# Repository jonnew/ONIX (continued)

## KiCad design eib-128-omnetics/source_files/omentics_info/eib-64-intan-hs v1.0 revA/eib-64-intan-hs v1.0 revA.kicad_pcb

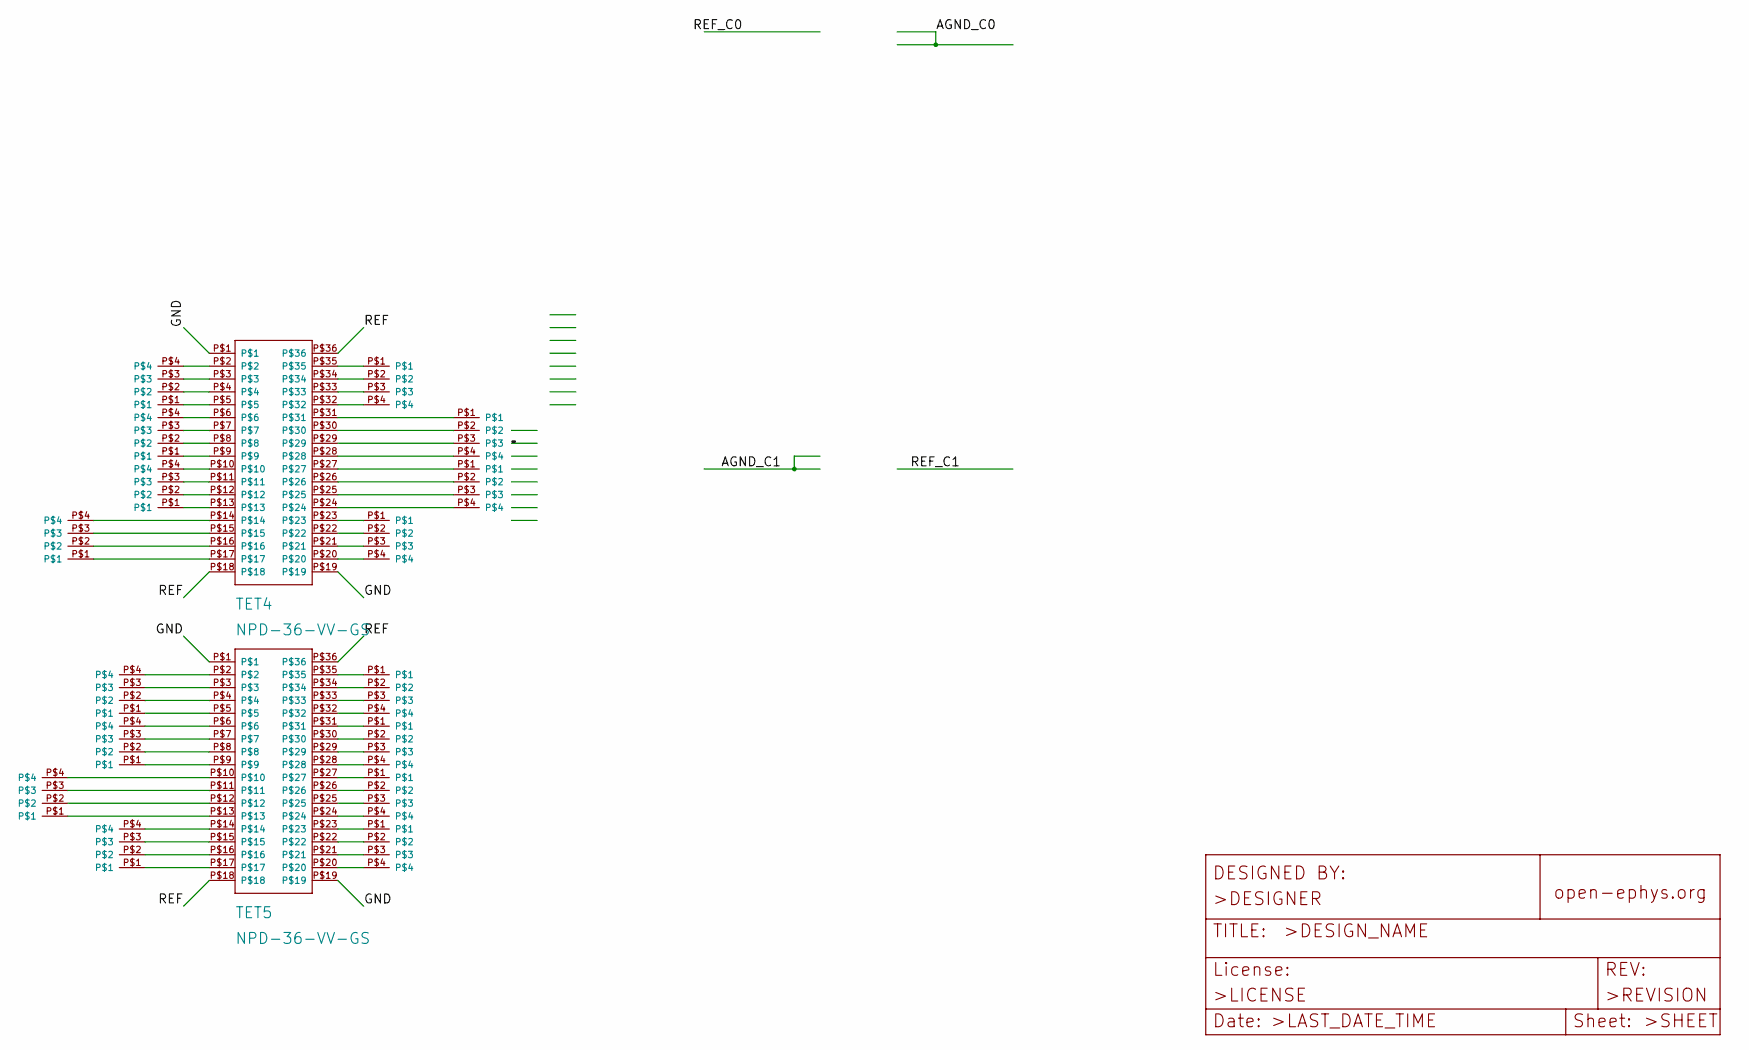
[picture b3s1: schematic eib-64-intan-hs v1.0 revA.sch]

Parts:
TET0: 0; TET32
TET1: 1; TET32
TET2: 2; TET32
TET3: 3; TET32
TET4, TET5: NPD-36-VV-GS
TET8: 8; TET32
TET9: 9; TET32
TET10: 10; TET32
TET11: 11; TET32
TET12: 12; TET32
TET13: 13; TET32
TET14: 14; TET32
TET15: 15; TET32
TET20: 20; TET32
TET21: 21; TET32
TET22: 22; TET32
TET23: 23; TET32

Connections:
/GND: TET4.P$1, TET4.P$19, TET5.P$1, TET5.P$19
/REF: TET4.P$18, TET4.P$36, TET5.P$18, TET5.P$36
unnamed: TET0.P$1, TET4.P$9
unnamed: TET0.P$2, TET4.P$8
unnamed: TET0.P$3, TET4.P$7
unnamed: TET0.P$4, TET4.P$6
unnamed: TET1.P$1, TET4.P$5
unnamed: TET1.P$2, TET4.P$4
unnamed: TET1.P$3, TET4.P$3
unnamed: TET1.P$4, TET4.P$2
unnamed: TET2.P$1, TET4.P$31
unnamed: TET2.P$2, TET4.P$30
unnamed: TET2.P$3, TET4.P$29
unnamed: TET2.P$4, TET4.P$28
unnamed: TET3.P$1, TET4.P$35
unnamed: TET3.P$2, TET4.P$34
unnamed: TET3.P$3, TET4.P$33
unnamed: TET3.P$4, TET4.P$32
unnamed: TET5.P$2, TET8.P$4
unnamed: TET5.P$3, TET8.P$3
unnamed: TET5.P$4, TET8.P$2
unnamed: TET5.P$5, TET8.P$1
unnamed: TET5.P$6, TET9.P$4
unnamed: TET5.P$7, TET9.P$3
unnamed: TET5.P$8, TET9.P$2
unnamed: TET5.P$9, TET9.P$1
unnamed: TET5.P$35, TET10.P$1
unnamed: TET5.P$34, TET10.P$2
unnamed: TET5.P$33, TET10.P$3
unnamed: TET5.P$32, TET10.P$4
unnamed: TET5.P$31, TET11.P$1
unnamed: TET5.P$30, TET11.P$2
unnamed: TET5.P$29, TET11.P$3
unnamed: TET5.P$28, TET11.P$4
unnamed: TET5.P$27, TET12.P$1
unnamed: TET5.P$26, TET12.P$2
unnamed: TET5.P$25, TET12.P$3
unnamed: TET5.P$24, TET12.P$4
unnamed: TET5.P$23, TET13.P$1
unnamed: TET5.P$22, TET13.P$2
unnamed: TET5.P$21, TET13.P$3
unnamed: TET5.P$20, TET13.P$4
unnamed: TET5.P$13, TET14.P$1
unnamed: TET5.P$12, TET14.P$2
unnamed: TET5.P$11, TET14.P$3
unnamed: TET5.P$10, TET14.P$4
unnamed: TET5.P$17, TET15.P$1
unnamed: TET5.P$16, TET15.P$2
unnamed: TET5.P$15, TET15.P$3
unnamed: TET5.P$14, TET15.P$4
unnamed: TET4.P$23, TET20.P$1
unnamed: TET4.P$22, TET20.P$2
unnamed: TET4.P$21, TET20.P$3
unnamed: TET4.P$20, TET20.P$4
unnamed: TET4.P$27, TET21.P$1
unnamed: TET4.P$26, TET21.P$2
unnamed: TET4.P$25, TET21.P$3
unnamed: TET4.P$24, TET21.P$4
unnamed: TET4.P$17, TET22.P$1
unnamed: TET4.P$16, TET22.P$2
unnamed: TET4.P$15, TET22.P$3
unnamed: TET4.P$14, TET22.P$4
unnamed: TET4.P$13, TET23.P$1
unnamed: TET4.P$12, TET23.P$2
unnamed: TET4.P$11, TET23.P$3
unnamed: TET4.P$10, TET23.P$4

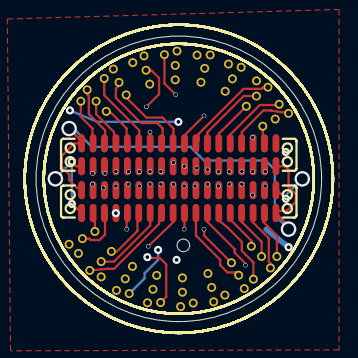
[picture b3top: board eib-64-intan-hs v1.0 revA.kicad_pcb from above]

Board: 4 copper layers, 15.9 x 15.9 mm, 19 parts (0 on the bottom side), 66 nets.

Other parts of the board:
@HOLE0: (no value)

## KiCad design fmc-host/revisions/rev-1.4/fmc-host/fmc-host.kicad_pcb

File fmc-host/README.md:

:warning: This headstage has moved to a dedicated repository: https://github.com/open-ephys/onix-fmc-host.
This folder should be considered archived.

# FMC Host Board
This card serves as host interface for serialized headstages and miniscopes, as
well as general purpose analog and digital IO. This board is a VITA-57.1
compliant module that uses high pin-count FMC connector. In combination with a
base FPGA board (e.g. [Numato Lab
Nereid](https://numato.com/product/nereid-kintex-7-pci-express-fpga-development-board),
it provides host PC communication for the following:

- Two deserailizers for any multifunction headstage conforming to our
  serialization protocol
- 12x 16-bit, +/-10V analog outputs or inputs. Direction selected via analog
  switch controllable over the FMC connector. Analog inputs are separated into
  2 simultaneously sampled 6-channel banks. When analog outputs are used, they
  are are always looped back using the analog inputs.
- 3x high speed LVDS input pairs
- 2x high speed LVDS outputs pairs
- 2x high speed, arbitrary logic-level, singled-ended lock inputs
- 1x high speed single ended, 50 ohm clock output
- 4x MLVDS input or output trigger lines

Easy access to IO is provided by the [breakout board](../breakout/README.md).

## Gerber Files
{% include gerber_layers.md %}

## Bill of Materials
The bill of materials for this device can be found
[here](https://docs.google.com/spreadsheets/d/1F-KWcdvH_63iXjZf0cgCfDiFX6XXW3qw6rlR8DZrFpQ/edit#gid=1976092058).

## Manufacturing Requirements
In order to meet approximately correct trace impedances, the design assumes the following stackup:

1. Top Copper 0.035 mm
1. Prepreg (2313\*1) 0.1 mm
1. Inner Copper 0.0175 mm
1. Core (Copper) 0.565 mm
1. Inner Copper 0.0175 mm
1. Prepeg (2116\*1) 0.127 mm
1. Inner Copper 0.0175 mm
1. Core (Copper) 0.565 mm
1. Inner Copper 0.0175 mm
1. Prepreg (2313\*1) 0.1 mm
1. Bottom Copper 0.0175 mm

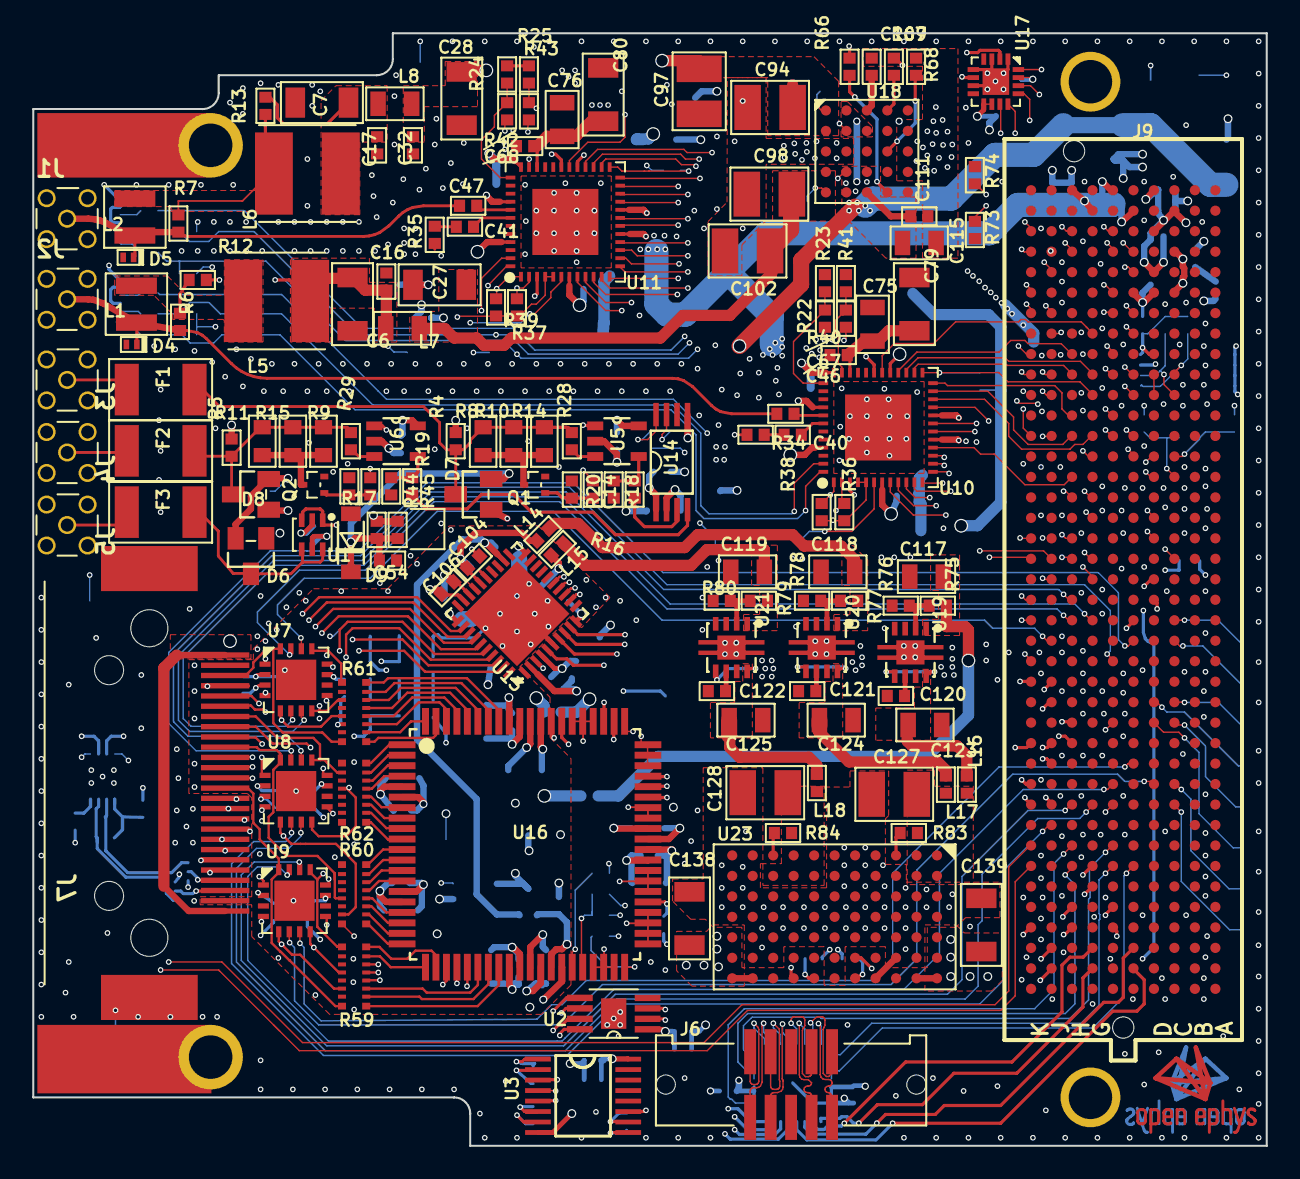
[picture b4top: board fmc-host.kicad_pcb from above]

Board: 6 copper layers, 76.5 x 69.0 mm, 321 parts (0 on the bottom side), 305 nets.

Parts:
C1, C2, C6, C7, C27, C28, C35, C36, C37, C38, C72, C73, C79, C80, C81, C91, C92, C138, C139, C140, C141: 10uF; 1206
C3, C4, C8, C9, C10, C11, C14, C15, C16, C17, C18, C19, C20, C23, C24, C31, C32, C33, C34, C39, C43, C45, C46, C47, C48, C49, C50, C51, C54, C55, C56, C58, C60, C62, C63, C65, C66, C67, C68, C78, C83, C84, C85, C86, C87, C89, C90, C93, C99, C100, C104, C106, C109, C110, C111, C113, C114, C129, C130, C131, C133, C134, C136, C137: 0.1uF; 0402
C5, C29, C30: 4.7nF; 0402
C12, C13, C21, C22, C25, C26, C52, C53, C57, C59, C82, C120, C121, C122: 10nF; 0402
C40, C41: 47nF; 0402
C42, C44, C69, C70, C74, C75, C76, C88: 1uF; 0805
C61, C64, C71, C77, C95, C96, C101, C103, C105, C107, C108, C112, C115, C116, C117, C118, C119, C123, C124, C125: 10uF; 0805
C94, C97, C98, C102, C126, C127, C128, C132, C135: 47uF; 1210
D1, D2, D3: HSMG-C280; LED-0402
D4, D5: SESD0402X1UN-0020-090; 0402P-DFN
D6, D7, D8: BAR66; SOT23
D9: KDZ4.3B; SOD123
D10, D11: APFA3011-AK13/F; RGB_LED_SMD-6
F1, F2, F3: C014F-2; 1812
J1, J2, J3, J4, J5: SMA002; MMCX-THRU
J6: ESHF-105-01-L-D-SM-K-TR
J7: 12226-8250-00FR; 12226-82X0-00XX
J8: 95278-101A16LF; JP2X8_SMD
J9: ASP-134488-01; FMC_HPC_MALE
L1, L2: 1008PS-472; 1008PS
L3, L4, L9, L10, L11, L12: BLM18KG601SN1D; 0603
L5, L6: SRNxx-101M; SRN6045TA
L7, L8: MPZ2012S102AT000; 0805
L13, L14, L15, L16, L17, L18: BLM15PX601SN1D; 0402
Q1, Q2: SI1012R; SC75
R1, R6, R7, R12, R13, R63, R64, R81, R82: 2k; 0402
R2, R3, R36, R37, R38, R39, R46, R49, R76, R78, R80: 4.7k; 0402
R4, R5, R23, R33, R44, R45: 3k; 0402
R8, R9, R10, R11, R14, R15: 150,0.25W; 0603
R16, R17, R55, R56, R57, R58, R83: 165k; 0402
R18, R19, R22, R40, R42, R65, R70, R71, R72, R73, R74, R85, R86: 10k; 0402
R20, R21, R47, R48, R50, R51, R52, R53: 1k; 0402
R24: 5.6k 1%; 0402
R25: 21k 1%; 0402
R26, R27: 60 1%; 0402
R28, R29, R34, R35: 49.9; 0402
R30, R31, R32: 100; 0402
R41, R43, R54, R69: 0; 0402
R59, R60, R61, R62: 2.2k; RN2X8-1506
R66, R67: 3.48k; 0402
R68: 649k; 0402
R75: 15k; 0402
R77, R79: 43k; 0402
R84: 178k; 0402
R87, R88: 73.2k; 0402
S1, S2: CHS-01TA; DIP01-SMD-GULL
S3: CHS-02TB
SJ1, SJ2: SJ2_0201; SJ_2_0201
TP1, TP2, TP4, TP5, TP6, TP7, TP11, TP12, TP13, TP14, TP15, TP16: TPB1,27; B1,27
TP3, TP8, TP9, TP10, TP17, TP18: TPB2,54; B2,54
U1: NC7WZ07P6X; SC70
U2: SN65LVDS9638DGN; MSOP-8-PAD-3X3
U3: FIN1032MTCX; TSSOP-16
U4: LTC2875_DFN; DFN83X3
U5, U6: ADCMP600; SOT-23-5
U7, U8, U9: DG1412E; QFN16-4X4MM
U10, U11: DS90UB934-Q1; WQFN48-7X7-PAD
U12: DS91M040; WQFN32-5X5
U13: AD5766BCPZ-RL7; CP_40_7
U14: MCP47FEB02A0-E/ST; TSSOP-8
U15: LM4132AMF-2.5/NOPBCT-ND; SOT-23-5
U16: AD7617BSTZ; ST_80_2
U17: AD5142BCPZ10; CP_16_27-L
U18: LTM4622A; BGA_5X5_625X625
U19, U20: TPS7A49; PVSON-N8+4-3X3
U21: TPS7A30; PVSON-N8+4-3X3
U22: 24ST; TSSOP8
U23: LTM8049_BGA; LTM8049
X2, X3: OE-LOGO_7X5; OE-LOGO-7X5
X4: FMC_SINGLE_WIDTH_MODULE

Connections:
+1V8: C86.2, C87.2, C91.2, C92.2, C135.2, C136.2, C137.2, J9.E39, J9.F40, J9.G39, J9.H40, L3.2, L4.2, L9.1, L10.1, R22.1, R24.1, R40.1, R42.1, TP16.TP, U10.17, U11.17
+3V3: C11.2, C23.1, C24.1, C29.1, C30.1, C33.1, C34.1, C39.1, C74.2, C78.2, C82.2, C89.2, C93.2, C96.2, C110.2, C112.2, C113.2, C116.2, C132.2, C133.2, C134.2, C138.1, C139.1, J9.C39, J9.D36, J9.D38, J9.D40, L11.1, L12.1, R36.2, R37.2, R38.2, R39.2, R46.2, R49.2, R63.2, R64.2, R69.1, R70.1, R71.1, R85.2, R86.2, S1.2, S2.2, TP11.TP, U1.5, U2.1, U3.4, U3.16, U4.3, U5.5, U6.5, U10.4, U10.5, U11.4, U11.5, U12.11, U12.12, U12.29, U12.30, U13.4, U14.1, U14.2, U16.49, U17.9, U17.10, U17.15, U23.A5, U23.A6, U23.A7, U23.B7, U23.K7, U23.L5, U23.L6, U23.L7
+12V: C115.2, C126.2, C129.2, C130.2, J7.1, J7.26, J9.C35, J9.C37, R44.2, R45.2, TP12.TP, U18.A2, U18.B3, U18.D3, U18.E2
/+5V_AN: C61.2, C64.2, C71.2, C77.2, C81.1, C83.2, C84.2, C85.2, C90.2, C106.2, C107.2, L13.1, R1.2, TP1.TP, U13.28, U15.3, U15.4, U16.6, U16.15, U16.30, U16.71
/+13V_AN: C8.2, C9.2, C10.2, C104.2, C105.2, L14.1, R2.2, TP2.TP, U7.11, U8.11, U9.11, U13.26
/-13V_AN: C18.2, C19.2, C20.2, C99.2, C103.2, L15.1, R3.2, TP4.TP, U7.2, U7.PAD, U8.2, U8.PAD, U9.2, U9.PAD, U13.6, U13.PAD
/ADC_BUSY: J9.J12, U16.67
/ADC_CONVST: J9.K13, U16.68
/ADC_MISO_A: J9.K11, U16.57
/ADC_MISO_B: J9.J10, U16.56
/ADC_MOSI: J9.K10, U16.55
/ADC_SCLK: J9.J13, U16.62
/ADDR0: J9.C27, R85.1, S3.4
/ADDR1: J9.C26, R86.1, S3.3
/AIN_AOUT0: J9.H19, U7.15
/AIN_AOUT1: J9.G19, U7.6
/AIN_AOUT2: J9.J18, U7.14
/AIN_AOUT3: J9.H20, U7.7
/AIN_AOUT4: J9.F17, U8.14
/AIN_AOUT5: J9.G10, U8.7
/AIN_AOUT6: J9.J9, U8.6
/AIN_AOUT7: J9.E18, U8.15
/AIN_AOUT8: J9.H10, U9.14
/AIN_AOUT9: J9.E12, U9.7
/AIN_AOUT10: J9.D11, U9.6
/AIN_AOUT11: J9.F11, U9.15
/AIO_0: J7.7, R59.C1, U9.16
/AIO_1: J7.20, R59.C3, U9.5
/AIO_2: J7.8, R59.C5, U9.8
/AIO_3: J7.21, R59.C8, U9.13
/AIO_4: J7.9, R60.C4, U8.16
/AIO_5: J7.22, R60.C2, U8.5
/AIO_6: J7.10, R62.C5, U8.8
/AIO_7: J7.23, R62.C7, U8.13
/AIO_8: J7.11, R61.C6, U7.8
/AIO_9: J7.24, R61.C8, U7.13
/AIO_10: J7.12, R61.C4, U7.5
/AIO_11: J7.25, R61.C1, U7.16
/AOUT0: U7.1, U13.32
/AOUT1: U7.4, U13.33
/AOUT2: U7.9, U13.34
/AOUT3: U7.12, U13.35
/AOUT4: U8.1, U13.36
/AOUT5: U8.4, U13.37
/AOUT6: U8.12, U13.38
/AOUT7: U8.9, U13.39
/AOUT8: U9.9, U13.12
/AOUT9: U9.12, U13.13
/AOUT10: U9.4, U13.14
/AOUT11: U9.1, U13.15
/CAN_RX: J9.K8, U4.4
/CAN_TX: J9.K7, U4.1
/CLKIN0: J9.D21, TP7.TP, U5.1
/CLKIN1: J9.E19, TP6.TP, U6.1
/CLKIN_TERM0: J9.K19, R20.1
/CLKIN_TERM1: J9.K17, R21.1
/CLKIN_VBIAS_SCL: J9.J21, R64.1, U14.7
/CLKIN_VBIAS_SDA: J9.K20, R63.1, U14.8
/CLKOUT: J9.D20, U1.1, U1.3
/DAC_MISO: J9.K16, U13.9
/DAC_MOSI: J9.H14, U13.5
/DAC_SCLK: J9.J15, U13.7
/DEBUG0: J8.2, J9.C10
/DEBUG1: J8.4, J9.C11
/DEBUG2: J8.6, J9.D14
/DEBUG3: J8.8, J9.C14
/DEBUG4: J8.10, J9.D15
/DEBUG5: J8.12, J9.C15
/DEBUG6: J8.14, J9.C18
/DEBUG7: J8.16, J9.C19
/DES_A_D0: J9.F34, U11.24
/DES_A_D1: J9.K35, U11.23
/DES_A_D2: J9.J34, U11.22
/DES_A_D3: J9.K34, U11.21
/DES_A_D4: J9.E33, U11.19
/DES_A_D5: J9.J33, U11.18
/DES_A_D6: J9.F32, U11.16
/DES_A_D7: J9.E31, U11.15
/DES_A_D8: J9.K32, U11.14
/DES_A_D9: J9.F31, U11.13
/DES_A_D10: J9.J31, U11.12
/DES_A_D11: J9.K31, U11.11
/DES_A_GPIO0: J9.J37, U11.28
/DES_A_GPIO1: J9.K37, U11.27
/DES_A_GPIO2: J9.J36, U11.26
/DES_A_GPIO3: J9.E34, R49.1, U11.25
/DES_A_HSYNC: J9.E30, U11.10
/DES_A_LEDG: J9.F28, R53.2
/DES_A_LOCK: J9.E27, R48.2, R56.2, U11.48
/DES_A_PASS: J9.J28, R51.2, R58.2, U11.47
/DES_A_PCLK: J9.K28, U11.8
/DES_A_PDB: J9.F35, U11.30
/DES_A_SCL: J9.F29, R37.1, U11.2
/DES_A_SDA\: J9.E28, R39.1, U11.1
/DES_A_VSYNC: J9.J30, U11.9
/DES_B_D0: J9.H29, U10.24
/DES_B_D1: J9.H28, U10.23
/DES_B_D2: J9.G28, U10.22
/DES_B_D3: J9.G27, U10.21
/DES_B_D4: J9.D27, U10.19
/DES_B_D5: J9.D26, U10.18
/DES_B_D6: J9.H26, U10.16
/DES_B_D7: J9.G25, U10.15
/DES_B_D8: J9.H25, U10.14
/DES_B_D9: J9.D24, U10.13
/DES_B_D10: J9.G24, U10.12
/DES_B_D11: J9.D23, U10.11
/DES_B_GPIO0: J9.H32, U10.28
/DES_B_GPIO1: J9.G31, U10.27
/DES_B_GPIO2: J9.H31, U10.26
/DES_B_GPIO3: J9.G30, R46.1, U10.25
/DES_B_HSYNC\: J9.H23, U10.10
/DES_B_LEDG: J9.G21, R52.2
/DES_B_LOCK: J9.J22, R47.2, R55.2, U10.48
/DES_B_PASS: J9.K22, R50.2, R57.2, U10.47
/DES_B_PCLK: J9.C22, U10.8
/DES_B_PDB: J9.G33, U10.30
/DES_B_SCL: J9.G22, R36.1, U10.2
/DES_B_SDA: J9.H22, R38.1, U10.1
/DES_B_VSYNC: J9.K23, U10.9
/DI_VBIAS0: R18.1, U14.3
/DI_VBIAS1: R19.1, U14.4
/DOUTP_F_A: C47.2, D5.C, J1.SIG, L2.2, R7.2
/DOUTP_F_B: C46.2, D4.C, J2.SIG, L1.2, R6.2
/LINK_A_PWR_EN: J9.H37, R74.1, U18.B2
/LINK_B_PWR_EN: J9.K38, R73.1, U18.D2
/LINK_PWR_ADJ_MISO: J9.F37, U17.13
/LINK_PWR_ADJ_MOSI: J9.E36, U17.12
/LINK_PWR_ADJ_SCLK: J9.H38, U17.11
/LVDS_DIN0: J9.J2, U3.3
/LVDS_DIN0_N: J7.4, R30.1, U3.1
/LVDS_DIN0_P: J7.17, R30.2, U3.2
/LVDS_DIN1: J9.H5, U3.5
/LVDS_DIN1_N: J7.16, R31.1, U3.7
/LVDS_DIN1_P: J7.3, R31.2, U3.6
/LVDS_DIN2: J9.H4, U3.11
/LVDS_DIN2_N/CAN_P: J7.2, SJ2.COM
/LVDS_DIN2_P/CAN_N: J7.15, SJ1.COM
/LVDS_DOUT0: J9.J3, U2.2
/LVDS_DOUT0_N: J7.19, U2.7
/LVDS_DOUT0_P: J7.6, U2.8
/LVDS_DOUT1: J9.K4, U2.3
/LVDS_DOUT1_N: J7.18, U2.5
/LVDS_DOUT1_P: J7.5, U2.6
/MLDVS_EN: J9.H8, U12.10
/MLDVS_RO0: J9.G2, U12.1
/MLDVS_RO1: J9.E3, U12.3
/MLDVS_RO2: J9.G7, U12.5
/MLDVS_RO3: J9.F4, U12.7
/MLVDS_DE_~RE0: J9.F7, U12.25, U12.26
/MLVDS_DE_~RE1: J9.E7, U12.27, U12.28
/MLVDS_DE_~RE2: J9.H7, U12.13, U12.14
/MLVDS_DE_~RE3: J9.F8, U12.15, U12.16
/MLVDS_DI0: J9.G3, U12.2
/MLVDS_DI1: J9.E2, U12.4
/MLVDS_DI2: J9.G6, U12.6
/MLVDS_DI3: J9.F5, U12.8
/SCL: J9.C30, R81.1, U22.6
/SDA: J9.C31, R82.1, U22.5
/TDI-TDO: J9.D30, J9.D31
/VAUX: C131.2, J9.D32, R81.2, R82.2, U22.8
/VDD_FPDX_A: C2.2, C4.2, C13.2, C22.2, C26.2, L4.1, U11.31, U11.40
/VDD_FPDX_B: C1.2, C3.2, C12.2, C21.2, C25.2, L3.1, U10.31, U10.40
/VDD_PX_A: C51.2, C53.2, C56.2, C59.2, C66.2, C73.2, L10.2, U11.36, U11.45
/VDD_PX_B: C50.2, C52.2, C55.2, C57.2, C65.2, C72.2, L9.2, U10.36, U10.45
/VLINK_A: C28.2, C32.1, C94.2, C97.2, L8.1, TP13.TP, U18.A1, U18.B1
/VLINK_B: C27.2, C31.1, C98.2, C102.2, L7.1, TP14.TP, U18.D1, U18.E1
/VREF: C88.2, R65.2, U13.22, U15.5
/V_PROTECT: C54.2, D6.2, D7.2, D8.2, D9.C, R44.1, R45.1, TP5.TP
/~ADC_CS: J9.H13, U16.63
/~ADC_RESET: J9.F10, R72.2
/~DAC_CS: J9.J16, U13.8
/~DAC_RESET: J9.F14, U13.3
/~LINK_PWR_ADJ_CS: J9.F38, U17.14
/~LINK_PWR_ADJ_RESET: J9.E37, U17.16
AGND: C8.1, C9.1, C10.1, C18.1, C19.1, C20.1, C61.1, C64.1, C71.1, C77.1, C81.2, C83.1, C84.1, C85.1, C88.1, C90.1, C95.1, C99.1, C100.1, C101.1, C103.1, C104.1, C105.1, C106.1, C107.1, D1.C, D2.C, D3.A, J7.13, J7.14, R54.1, R59.C2, R59.C4, R59.C6, R59.C7, R60.C1, R60.C3, R60.C5, R60.C6, R60.C7, R60.C8, R61.C2, R61.C3, R61.C5, R61.C7, R62.C1, R62.C2, R62.C3, R62.C4, R62.C6, R62.C8, TP3.TP, U7.3, U8.3, U9.3, U13.10, U13.20, U13.23, U13.24, U13.25, U13.29, U13.31, U15.2, U16.5, U16.16, U16.29, U16.32, U16.34, U16.69, U16.72
GND: C1.1, C2.1, C3.1, C4.1, C5.2, C6.1, C7.1, C11.1, C12.1, C13.1, C14.2, C15.2, C16.2, C17.2, C21.1, C22.1, C23.2, C24.2, C25.1, C26.1, C27.1, C28.1, C29.2, C30.2, C31.2, C32.2, C33.2, C34.2, C35.1, C36.1, C37.1, C38.1, C39.2, C42.1, C43.1, C44.1, C45.1, C48.1, C49.1, C50.1, C51.1, C52.1, C53.1, C54.1, C55.1, C56.1, C57.1, C58.1, C59.1, C60.1, C62.1, C63.1, C65.1, C66.1, C67.1, C68.1, C69.1, C70.1, C72.1, C73.1, C74.1, C75.1, C76.1, C78.1, C79.1, C80.1, C82.1, C86.1, C87.1, C89.1, C91.1, C92.1, C93.1, C94.1, C96.1, C97.1, C98.1, C102.1, C108.1, C109.1, C110.1, C111.1, C112.1, C113.1, C114.2, C115.1, C116.1, C117.1, C118.1, C119.1, C120.2, C121.2, C122.2, C123.1, C124.1, C125.1, C126.1, C127.1, C128.2, C129.1, C130.1, C131.1, C132.1, C133.1, C134.1, C135.1, C136.1, C137.1, C138.2, C139.2, C140.1, C141.1, D4.A, D5.A, D6.1, D7.1, D8.1, D9.A, D10.3, D10.5, D10.6, D11.3, D11.5, D11.6, J1.GND@1, J1.GND@2, J1.GND@3, J1.GND@4, J2.GND@1, J2.GND@2, J2.GND@3, J2.GND@4, J3.GND@1, J3.GND@2, J3.GND@3, J3.GND@4, J4.GND@1, J4.GND@2, J4.GND@3, J4.GND@4, J5.GND@1, J5.GND@2, J5.GND@3, J5.GND@4, J7.PAD1, J7.PAD2, J8.1, J8.3, J8.5, J8.7, J8.9, J8.11, J8.13, J8.15, J9.A1, J9.A4, J9.A5, J9.A8, J9.A9, J9.A12, J9.A13, J9.A16, J9.A17, J9.A20, J9.A21, J9.A24, J9.A25, J9.A28, J9.A29, J9.A32, J9.A33, J9.A36, J9.A37, J9.A40, J9.B2, J9.B3, J9.B6, J9.B7, J9.B10, J9.B11, J9.B14, J9.B15, J9.B18, J9.B19, J9.B22, J9.B23, J9.B26, J9.B27, J9.B30, J9.B31, J9.B34, J9.B35, J9.B38, J9.B39, J9.C1, J9.C4, J9.C5, J9.C8, J9.C9, J9.C12, J9.C13, J9.C16, J9.C17, J9.C20, J9.C21, J9.C24, J9.C25, J9.C28, J9.C29, J9.C32, J9.C33, J9.C34, J9.C36, J9.C38, J9.C40, J9.D2, J9.D3, J9.D6, J9.D7, J9.D10, J9.D13, J9.D16, J9.D19, J9.D22, J9.D25, J9.D28, J9.D35, J9.D37, J9.D39, J9.E1, J9.E4, J9.E5, J9.E8, J9.E11, J9.E14, J9.E17, J9.E20, J9.E23, J9.E26, J9.E29, J9.E32, J9.E35, J9.E38, J9.E40, J9.F2, J9.F3, J9.F6, J9.F9, J9.F12, J9.F15, J9.F18, J9.F21, J9.F24, J9.F27, J9.F30, J9.F33, J9.F36, J9.F39, J9.G1, J9.G4, J9.G5, J9.G8, J9.G11, J9.G14, J9.G17, J9.G20, J9.G23, J9.G26, J9.G29, J9.G32, J9.G35, J9.G38, J9.G40, J9.H3, J9.H6, J9.H9, J9.H12, J9.H15, J9.H18, J9.H21, J9.H24, J9.H27, J9.H30, J9.H33, J9.H36, J9.H39, J9.J1, J9.J4, J9.J5, J9.J8, J9.J11, J9.J14, J9.J17, J9.J20, J9.J23, J9.J26, J9.J29, J9.J32, J9.J35, J9.J38, J9.J40, J9.K2, J9.K3, J9.K6, J9.K9, J9.K12, J9.K15, J9.K18, J9.K21, J9.K24, J9.K27, J9.K30, J9.K33, J9.K36, J9.K39, Q1.2, Q2.2, R4.1, R5.1, R16.1, R17.1, R23.2, R25.2, R33.1, R34.2, R35.2, R41.2, R43.2, R54.2, R55.1, R56.1, R57.1, R58.1, R68.2, R73.2, R74.2, R76.1, R78.1, R80.1, R87.2, R88.2, S3.1, S3.2, TP8.TP, TP9.TP, TP10.TP, TP17.TP, TP18.TP, U1.2, U2.4, U2.PAD, U3.8, U3.12, U4.2, U4.PAD, U5.2, U6.2, U10.43, U10.44, U10.46, U10.PAD, U11.43, U11.44, U11.46, U11.PAD, U12.31, U12.PAD, U13.2, U14.5, U14.6, U16.37, U16.38, U16.39, U16.41, U16.42, U16.43, U16.44, U16.46, U16.47, U16.48, U16.50, U16.51, U16.53, U16.54, U16.58, U16.59, U16.60, U16.61, U16.64, U16.65, U16.66, U17.1, U17.3, U17.5, U17.7, U17.PAD, U18.B5, U18.C1, U18.C2, U18.C5, U18.D5, U19.3, U19.4, U19.PAD1, U19.PAD2, U19.PAD3, U19.PAD4, U19.PAD5, U20.3, U20.4, U20.PAD1, U20.PAD2, U20.PAD3, U20.PAD4, U20.PAD5, U21.3, U21.4, U21.PAD1, U21.PAD2, U21.PAD3, U21.PAD4, U21.PAD5, U22.1, U22.2, U22.3, U22.4, U22.7, U23.A3, U23.A4, U23.B3, U23.B4, U23.B5, U23.B6, U23.C2, U23.C3, U23.C4, U23.C5, U23.C6, U23.D1, U23.D2, U23.D3, U23.D4, U23.D5, U23.D7, U23.E1, U23.E2, U23.E3, U23.E4, U23.E5, U23.F1, U23.F2, U23.F5, U23.F6, U23.F7, U23.G3, U23.G4, U23.G5, U23.H3, U23.H4, U23.H5, U23.J3, U23.J4, U23.J5, U23.J6, U23.K1, U23.K2, U23.K3, U23.K4, U23.K5, U23.K6, U23.L1, U23.L2, U23.L3, U23.L4
unnamed: C5.1, R26.1, R27.1, U4.5
unnamed: C14.1, R18.2, U5.4
unnamed: C15.1, R19.2, U6.4
unnamed: C6.2, C16.1, L5.1, L7.2, R12.1
unnamed: C7.2, C17.1, L6.1, L8.2, R13.1
unnamed: C35.2, C42.2, C48.2, U10.3
unnamed: C36.2, C43.2, U10.20
unnamed: C37.2, C44.2, C49.2, U11.3
unnamed: C38.2, C45.2, U11.20
unnamed: C40.1, U10.42
unnamed: C40.2, R34.1
unnamed: C41.1, U11.42
unnamed: C41.2, R35.1
unnamed: C46.1, U10.41
unnamed: C47.1, U11.41
unnamed: C67.2, C75.2, C79.2, U10.34
unnamed: C68.2, C76.2, C80.2, U11.34
unnamed: C95.2, U16.31
unnamed: C100.2, R65.1, U16.33
unnamed: C101.2, U16.70
unnamed: C108.2, U16.52
unnamed: C109.2, U18.A3
unnamed: C111.2, U18.E3
unnamed: C114.1, R72.1, U16.36
unnamed: C117.2, L13.2, R75.2, U19.1
unnamed: C118.2, L14.2, R77.2, U20.1
unnamed: C119.2, L15.2, R79.2, U21.1
unnamed: C120.1, U19.6
unnamed: C121.1, U20.6
unnamed: C122.1, U21.6
unnamed: C123.2, L16.1, U19.5, U19.8
unnamed: C124.2, L17.1, U20.5, U20.8
unnamed: C125.2, L18.1, U21.5, U21.8
unnamed: C127.2, L16.2, L17.2, R83.1, U23.A1, U23.A2, U23.B1, U23.B2
unnamed: C128.1, L18.2, R84.1, U23.G1, U23.G2, U23.H1, U23.H2, U23.J2
unnamed: C60.2, C63.2, C70.2, C140.2, L12.2, U11.7, U11.29
unnamed: C58.2, C62.2, C69.2, C141.2, L11.2, U10.7, U10.29
unnamed: D1.A, R1.1
unnamed: D2.A, R2.1
unnamed: D3.C, R3.1
unnamed: D6.3, F3.2, U1.4, U1.6
unnamed: D7.3, F1.2, R4.2, R8.2, R10.2, R14.2, R28.1
unnamed: D8.3, F2.2, R5.2, R9.2, R11.2, R15.2, R29.1
unnamed: D10.1, R47.1
unnamed: D10.2, R50.1
unnamed: D10.4, R52.1
unnamed: D11.1, R48.1
unnamed: D11.2, R51.1
unnamed: D11.4, R53.1
unnamed: F1.1, J3.SIG
unnamed: F2.1, J4.SIG
unnamed: F3.1, J5.SIG
unnamed: J6.1, U12.18
unnamed: J6.2, U12.17
unnamed: J6.3, U12.20
unnamed: J6.4, U12.19
unnamed: J6.7, U12.22
unnamed: J6.8, U12.21
unnamed: J6.9, U12.24
unnamed: J6.10, U12.23
unnamed: L1.1, L5.2, R6.1, R12.2
unnamed: L2.1, L6.2, R7.1, R13.2
unnamed: Q1.1, R16.2, R20.2
unnamed: Q1.3, R8.1, R10.1, R14.1
unnamed: Q2.1, R17.2, R21.2
unnamed: Q2.3, R9.1, R11.1, R15.1
unnamed: R22.2, R23.1, U10.37
unnamed: R24.2, R25.1, U11.37
unnamed: R26.2, SJ2.2, U4.7
unnamed: R27.2, SJ1.2, U4.6
unnamed: R28.2, U5.3
unnamed: R29.2, U6.3
unnamed: R32.1, SJ2.1, U3.9
unnamed: R32.2, SJ1.1, U3.10
unnamed: R33.2, U4.8
unnamed: R40.2, R41.1, U10.35
unnamed: R42.2, R43.1, U11.35
unnamed: R59.1, U16.28
unnamed: R59.2, U16.27
unnamed: R59.3, U16.26
unnamed: R59.4, U16.25
unnamed: R59.5, U16.24
unnamed: R59.6, U16.23
unnamed: R59.7, U16.21
unnamed: R59.8, U16.22
unnamed: R60.1, U16.20
unnamed: R60.2, U16.19
unnamed: R60.3, U16.18
unnamed: R60.4, U16.17
unnamed: R60.5, U16.14
unnamed: R60.6, U16.13
unnamed: R60.7, U16.12
unnamed: R60.8, U16.11
unnamed: R61.1, U16.79
unnamed: R61.2, U16.80
unnamed: R61.3, U16.78
unnamed: R61.4, U16.77
unnamed: R61.5, U16.76
unnamed: R61.6, U16.75
unnamed: R61.7, U16.74
unnamed: R61.8, U16.73
unnamed: R62.1, U16.10
unnamed: R62.2, U16.9
unnamed: R62.3, U16.8
unnamed: R62.4, U16.7
unnamed: R62.5, U16.4
unnamed: R62.6, U16.3
unnamed: R62.7, U16.2
unnamed: R62.8, U16.1
unnamed: R66.1, U18.E4
unnamed: R66.2, U17.2
unnamed: R67.1, U18.A4
unnamed: R67.2, U17.6
unnamed: R68.1, U18.C4
unnamed: R69.2, U16.35
unnamed: R70.2, U16.40
unnamed: R71.2, U16.45
unnamed: R75.1, R76.2, U19.2
unnamed: R77.1, R78.2, U20.2
unnamed: R79.1, R80.2, U21.2
unnamed: R83.2, U23.C1
unnamed: R84.2, U23.J1
unnamed: R87.1, U23.E7
unnamed: R88.1, U23.G7
unnamed: S1.1, U10.6
unnamed: S2.1, U11.6
unnamed: TP15.TP, U13.27
unnamed: U23.E6, U23.H7

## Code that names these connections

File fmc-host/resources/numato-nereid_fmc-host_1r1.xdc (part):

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set_property -dict { PACKAGE_PIN "AE25"   IOSTANDARD LVCMOS33       SLEW FAST} [get_ports { LA04_N              }]   ;          # IO_L23N_T3_12                 Sch = LA04_N            FMC = H11
set_property -dict { PACKAGE_PIN "W25"    IOSTANDARD LVCMOS33       SLEW FAST} [get_ports { AIN/OUT9            }]   ;          # IO_L5P_T0_12                  Sch = LA05_P            FMC = D11
set_property -dict { PACKAGE_PIN "W26"    IOSTANDARD LVCMOS33       SLEW FAST} [get_ports { LA05_N              }]   ;          # IO_L5N_T0_12                  Sch = LA05_N            FMC = D12
set_property -dict { PACKAGE_PIN "Y25"    IOSTANDARD LVCMOS33       SLEW FAST} [get_ports { DEBUG0              }]   ;          # IO_L10P_T1_12                 Sch = LA06_P            FMC = C10
set_property -dict { PACKAGE_PIN "Y26"    IOSTANDARD LVCMOS33       SLEW FAST} [get_ports { DEBUG1              }]   ;          # IO_L10N_T1_12                 Sch = LA06_N            FMC = C11
set_property -dict { PACKAGE_PIN "V23"    IOSTANDARD LVCMOS33       SLEW FAST} [get_ports { ADC_CONVST          }]   ;          # IO_L3P_T0_DQS_12              Sch = LA07_P            FMC = H13
set_property -dict { PACKAGE_PIN "V24"    IOSTANDARD LVCMOS33       SLEW FAST} [get_ports { DAC_MOSI            }]   ;          # IO_L3N_T0_DQS_12              Sch = LA07_N            FMC = H14
set_property -dict { PACKAGE_PIN "U26"    IOSTANDARD LVCMOS33       SLEW FAST} [get_ports { LA08_P              }]   ;          # IO_L4P_T0_12                  Sch = LA08_P            FMC = G12
set_property -dict { PACKAGE_PIN "V26"    IOSTANDARD LVCMOS33       SLEW FAST} [get_ports { LA08_N              }]   ;          # IO_L4N_T0_12                  Sch = LA08_N            FMC = G13
set_property -dict { PACKAGE_PIN "W20"    IOSTANDARD LVCMOS33       SLEW FAST} [get_ports { DEBUG2              }]   ;          # IO_L15P_T2_DQS_12             Sch = LA09_P            FMC = D14
set_property -dict { PACKAGE_PIN "Y21"    IOSTANDARD LVCMOS33       SLEW FAST} [get_ports { DEBUG4              }]   ;          # IO_L15N_T2_DQS_12             Sch = LA09_N            FMC = D15
set_property -dict { PACKAGE_PIN "V21"    IOSTANDARD LVCMOS33       SLEW FAST} [get_ports { DEBUG3              }]   ;          # IO_L6P_T0_12                  Sch = LA10_P            FMC = C14
set_property -dict { PACKAGE_PIN "W21"    IOSTANDARD LVCMOS33       SLEW FAST} [get_ports { DEBUG5              }]   ;          # IO_L6N_T0_VREF_12             Sch = LA10_N            FMC = C15
set_property -dict { PACKAGE_PIN "L19"    IOSTANDARD LVCMOS33       SLEW FAST} [get_ports { LA11_P              }]   ;          # IO_L21P_T3_DQS_15             Sch = LA11_P            FMC = H16
set_property -dict { PACKAGE_PIN "L20"    IOSTANDARD LVCMOS33       SLEW FAST} [get_ports { LA11_N              }]   ;          # IO_L21N_T3_DQS_A18_15         Sch = LA11_N            FMC = H17
set_property -dict { PACKAGE_PIN "M17"    IOSTANDARD LVCMOS33       SLEW FAST} [get_ports { LA12_P              }]   ;          # IO_L23P_T3_FOE_B_15           Sch = LA12_P            FMC = G15
set_property -dict { PACKAGE_PIN "L18"    IOSTANDARD LVCMOS33       SLEW FAST} [get_ports { LA12_N              }]   ;          # IO_L23N_T3_FWE_B_15           Sch = LA12_N            FMC = G16
set_property -dict { PACKAGE_PIN "K20"    IOSTANDARD LVCMOS33       SLEW FAST} [get_ports { LA13_P              }]   ;          # IO_L19P_T3_A22_15             Sch = LA13_P            FMC = D17
set_property -dict { PACKAGE_PIN "J20"    IOSTANDARD LVCMOS33       SLEW FAST} [get_ports { LA13_N              }]   ;          # IO_L19N_T3_A21_VREF_15        Sch = LA13_N            FMC = D18
set_property -dict { PACKAGE_PIN "J18"    IOSTANDARD LVCMOS33       SLEW FAST} [get_ports { DEBUG6              }]   ;          # IO_L20P_T3_A20_15             Sch = LA14_P            FMC = C18
set_property -dict { PACKAGE_PIN "J19"    IOSTANDARD LVCMOS33       SLEW FAST} [get_ports { DEBUG7              }]   ;          # IO_L20N_T3_A19_15             Sch = LA14_N            FMC = C19
set_property -dict { PACKAGE_PIN "U17"    IOSTANDARD LVCMOS33       SLEW FAST} [get_ports { AIN/OUT0            }]   ;          # IO_L23P_T3_13                 Sch = LA15_P            FMC = H19
set_property -dict { PACKAGE_PIN "T17"    IOSTANDARD LVCMOS33       SLEW FAST} [get_ports { LA15_N              }]   ;          # IO_L23N_T3_13                 Sch = LA15_N            FMC = H20
set_property -dict { PACKAGE_PIN "T18"    IOSTANDARD LVCMOS33       SLEW FAST} [get_ports { AIN/OUT2            }]   ;          # IO_L19P_T3_13                 Sch = LA16_P            FMC = G18
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set_property -dict { PACKAGE_PIN "H18"    IOSTANDARD LVCMOS33       SLEW FAST} [get_ports { LA30_N              }]   ;          # IO_L14N_T2_SRCC_15            Sch = LA30_N            FMC = H35
set_property -dict { PACKAGE_PIN "G19"    IOSTANDARD LVCMOS33       SLEW FAST} [get_ports { DES_PDN_B           }]   ;          # IO_L16P_T2_A28_15             Sch = LA31_P            FMC = G33
set_property -dict { PACKAGE_PIN "F20"    IOSTANDARD LVCMOS33       SLEW FAST} [get_ports { LA31_N              }]   ;          # IO_L16N_T2_A27_15             Sch = LA31_N            FMC = G34
set_property -dict { PACKAGE_PIN "H19"    IOSTANDARD LVCMOS33       SLEW FAST} [get_ports { LINK_A_PWR_EN       }]   ;          # IO_L18P_T2_A24_15             Sch = LA32_P            FMC = H37
set_property -dict { PACKAGE_PIN "G20"    IOSTANDARD LVCMOS33       SLEW FAST} [get_ports { LINK_PWR_ADJ_SCLK   }]   ;          # IO_L18N_T2_A23_15             Sch = LA32_N            FMC = H38
set_property -dict { PACKAGE_PIN "L17"    IOSTANDARD LVCMOS33       SLEW FAST} [get_ports { LA33_P              }]   ;          # IO_L24P_T3_RS1_15             Sch = LA33_P            FMC = G36
set_property -dict { PACKAGE_PIN "K18"    IOSTANDARD LVCMOS33       SLEW FAST} [get_ports { LA33_N              }]   ;          # IO_L24N_T3_RS0_15             Sch = LA33_N            FMC = G37
set_property -dict { PACKAGE_PIN "P23"    IOSTANDARD LVCMOS33       SLEW FAST} [get_ports { MLVDS_DI_1          }]   ;          # IO_L11P_T1_SRCC_13            Sch = HA00_CC_P         FMC = F4
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set_property -dict { PACKAGE_PIN "M20"    IOSTANDARD LVCMOS33       SLEW FAST} [get_ports { HA04_N              }]   ;          # IO_L7N_T1_13                  Sch = HA04_N            FMC = F8
set_property -dict { PACKAGE_PIN "R18"    IOSTANDARD LVCMOS33       SLEW FAST} [get_ports { HA05_P              }]   ;          # IO_L24P_T3_13                 Sch = HA05_P            FMC = E6
set_property -dict { PACKAGE_PIN "P18"    IOSTANDARD LVCMOS33       SLEW FAST} [get_ports { HA05_N              }]   ;          # IO_L24N_T3_13                 Sch = HA05_N            FMC = E7
set_property -dict { PACKAGE_PIN "P16"    IOSTANDARD LVCMOS33       SLEW FAST} [get_ports { ADC_MOSI            }]   ;          # IO_L20P_T3_13                 Sch = HA06_P            FMC = K10
set_property -dict { PACKAGE_PIN "N17"    IOSTANDARD LVCMOS33       SLEW FAST} [get_ports { ADC_MISO_A          }]   ;          # IO_L20N_T3_13                 Sch = HA06_N            FMC = K11
set_property -dict { PACKAGE_PIN "R16"    IOSTANDARD LVCMOS33       SLEW FAST} [get_ports { AIN/OUT5            }]   ;          # IO_L21P_T3_DQS_13             Sch = HA07_P            FMC = J9
set_property -dict { PACKAGE_PIN "R17"    IOSTANDARD LVCMOS33       SLEW FAST} [get_ports { ADC_MISO_B          }]   ;          # IO_L21N_T3_DQS_13             Sch = HA07_N            FMC = J10
set_property -dict { PACKAGE_PIN "U19"    IOSTANDARD LVCMOS33       SLEW FAST} [get_ports { nADC_RESET          }]   ;          # IO_L18P_T2_13                 Sch = HA08_P            FMC = F10
set_property -dict { PACKAGE_PIN "U20"    IOSTANDARD LVCMOS33       SLEW FAST} [get_ports { AIN/OUT8            }]   ;          # IO_L18N_T2_13                 Sch = HA08_N            FMC = F11
set_property -dict { PACKAGE_PIN "N18"    IOSTANDARD LVCMOS33       SLEW FAST} [get_ports { HA09_P              }]   ;          # IO_L22P_T3_13                 Sch = HA09_P            FMC = E9
set_property -dict { PACKAGE_PIN "M19"    IOSTANDARD LVCMOS33       SLEW FAST} [get_ports { HA09_N              }]   ;          # IO_L22N_T3_13                 Sch = HA09_N            FMC = E10
set_property -dict { PACKAGE_PIN "T20"    IOSTANDARD LVCMOS33       SLEW FAST} [get_ports { nADC_CS             }]   ;          # IO_L16P_T2_13                 Sch = HA10_P            FMC = K13
set_property -dict { PACKAGE_PIN "R20"    IOSTANDARD LVCMOS33       SLEW FAST} [get_ports { HA10_N              }]   ;          # IO_L16N_T2_13                 Sch = HA10_N            FMC = K14
set_property -dict { PACKAGE_PIN "P19"    IOSTANDARD LVCMOS33       SLEW FAST} [get_ports { ADC_BUSY            }]   ;          # IO_L9P_T1_DQS_13              Sch = HA11_P            FMC = J12
set_property -dict { PACKAGE_PIN "P20"    IOSTANDARD LVCMOS33       SLEW FAST} [get_ports { ADC_SCLK            }]   ;          # IO_L9N_T1_DQS_13              Sch = HA11_N            FMC = J13
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
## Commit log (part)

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2018-04-24 Reorganized and revised system specification
    - Up to date
    - Logical devision of content
    - Updated API documentation
2018-05-18 Replaced stim null circuit on both headstages
    - ADG140x was replaced with dg509b, which is a 2 circuit 1-to-4 mux.
    This allows the electrode path to be completely disconnected from
    stimulation circuitry during idle periods. During idle periods,
    stimuluation output is shunted to ground through a dummy load so that
    offsets to not develop large voltages during idle periods.
    - Additionally, the inverting node of the estim current source amplifier
2018-07-09 headstage-256 rev 1.1
    - Should be ready for speedy
    - 8 layer board should fix radio-freq isolation issue on previous
    version
    - Other small circuit modifications and fixes
2018-07-18 pcie-host board rev. 1.2
    - Extra bidirectional isolator added to propogate LOCK and PASS signals from deserializer to host FPGA.
    - Immediate non-isolated and isolated SMA IO added.
    - Routed HSYNC to normal (LA) differential pins rather than dedicated
    clock input which was causing synthesis issues.
2018-07-20 Improvements to clroepcie
    - Overloads for get_opt directly in clr binding. Should do this for
    set_opt as well and get rid of DispoIntPtr entirely.
2018-07-23 Bring Intan AUX inputs to eib-256 from headstage-256
    - There were several unused pins on eib-256.
    - I brought two of the Intan AUX inputs from amplifiers A and B and one
    from C and D to these unused pins. Test point connections on the
    headstage were preserved.
    - eib-128 will not be modified because these pins use the amp C
    and D headers. A and B headers are occupied with e/o-stim connections.
2018-07-25 Produced gerbers for headstage-256 rev. 1.1
    - Should be ready for production
    - Updated schematic
2018-07-30 Added sizing sketch for mezzanine board on headstage-64
2018-08-10 Many fixes to new 8-layer routing
    - Replace ultra thin power traces
    - Proper z on differential pairs
    - Decoupling elements moved to corresponding ICs
    - Remove thin gnd wiring and use planes
2018-08-17 Updated headstage-256 revision to 1.1.
2018-08-22 Update deprated serdes-interface to most current version
    - FPGA moved to top
    - Estim circuit
2018-08-27 eib-64 rev. 1.1
    - Fits latest shuttle drive reatining feature.
2018-10-07 headstage-256 rev 1.1 and headstage-64 rev. 1.2
    - These should be ready for fabrication
    - Extensive DRU and manual checking on both designs
    - Howland current source integrated into both designs
    - MPU9250 replace with ICM-20948 on headstage-64 since MPU is deprecated
    - Gerbers update and gerbv project files as well
    - Schematics of both headstages updated
2018-10-14 Github site update
    - Bring READMEs up to date, more or less
    - Files for local Jekyll build
    - All pdfs, images, etc moved to LFS
2018-10-27 Make liboepcie thread safe
    - Be careful -- performance hit in some cases because we are funneling
    through syscalls
2018-11-01 Update xillybus backend instructions
    - Included high bw write stream
    - Fix broken image link
2018-12-05 Fixed mising vcoax trace on bno55 variant
2018-12-23 WIP of version 2.1.0 of oepcie API
    - oe_write_frame() prototype replaced with oe_write(), which can write
    block data to particular devices.
    - Block read size is now a context option
    - CLR and C++ bindings implement c library changes and appear to work.
    - More extensive testing is required
    - API docs and spec need to be updated
2019-01-02 Minor changes to headstage-64 while updating BOM
    - stencil size reduced for dfn diode packages to prevent shorting
2019-01-20 FMC host module
    - This will deprecate pcie-host
    - Should conform, largely, to VITA-57 standardFeatures
    - 1 deserializer
    - 2 arbitrary logic-level rugged GPIs
    - 1 arbitrary logic-level rugged GPO
    - 8 16-bit analog outputs
2019-01-23 Moved vias in io breakout away from screws
2019-01-23 Update gerbers for analog-io-breakout board
2019-01-24 Connected screw terminal rows in analog io board
2019-02-10 Minor changes to liboepcie during debugging
    - Added test device
2019-02-25 updated breakout board shell
2019-03-02 Fixed BNC footprint in analog-io-breakout -also added grounded mounting hole and fixed label spacing
2019-03-05 Updates to fmc-breakout after talking with Jakob
    - Moved origin to upper left corner
    - Increased hole sizes on BNC connectors
    - Moved high speed section to top of board s.t. it is next to the other
    input connector
2019-03-06 Increased size of BNC through holes on breakout board
    - As per jakob's request
2019-04-29 Some minor api modifications and fixes
    - Remove unessesary resets from acquisition startup since this is handled
    in oe_init_ctx
2019-06-03 Fix syntax error in oelogo.h
    - Dangling string after ;
2019-07-28 Lighthouse-booster Rev. 1.1
    - Minor fixes to version 1.0 after testing
    - Replaced 0 ohm jumpers between gate driver and gate with 47 kOhm
    pulldowns to prevent possible DC damage to LEDs when board is not
    driven
    - Decrease current limit resistors to 360 mOhm. This should give us 5
    Amps per LED string after empirical testing
2019-07-29 Added Speedy order number to fabrication file README
2019-08-09 Added LMK61E2
    Should solve the issue of how to make 93.6 MHz, but is pretty huge
2019-08-12 fmc-host rev. 1.1
    - Completed revision 1.1 of the FMC host module
    - Needs final synthesis testing before fab
2019-08-16 Breakout board WIP
    - added shiftreg to read keys and relay status
    - added power supply
    - added relays
    - added lvds/se converters
2019-08-19 Fixed flat-flex connector part number on headstage-neuropix
    - Also, updated PDF of schematic
2019-08-22 Added encoder datasheet
2019-08-26 Breakout board layout and circuit fixes
    - Many fixes to schematic ERC and board layout
    - Added serial to parallel digital IO
2019-08-29 Update headstage-64 and headstage-256 schematics
    - I did this while double checking the BOM for Filipe
    - Divide functional blocks into labeled sections
    - Add images of schematics to the READMEs
2019-09-01 breakout case WIP
2019-09-22 Add smd centroids to headstage-64
2019-09-27 Lighthouse booster rev. 1.2
    - Added a monostable vibrator to the high-side power-switch trigger
    circuit in order to prevent the system 12V from seeing any of the LED
    circuit when the LEDs are active.
    - This circuit re-triggers on every incoming sync pulse so that a
    perfect envelope is formed to disconnected the system 12V from the LED
    12V whenever a sync train is being applied
2019-10-02 added first draft of 128 EIB with omnetics connectors
2019-10-07 Added some very rudimentary firmware for the breakout board
    - Display a main menu on the OLED using littlevgl
    - Control it with a rotary encoder
    - littlevgl config file is included and needs to be copied to the base
    directory of the littlevgl library before using this
2019-10-30 Update API with neuropixels 1.0 device definitions
2019-11-17 Updates to fmc-host board when testing revision 1.3
    - This is starting revision 1.4
    - Replaced SPDT analog switches for analog IO with SPST swiches inline
    with the analog outpus. Inputs are always connected. This allows
    loopback of analog output instead of wasting the analog input
    capabilites when a line is selected to be an output
2019-11-22 Fix wrong paths in test app
2019-11-25 Update EIBs and add eib-64-large
    - eib-64-large is identical to eib-64, except that it fits large shuttle
    drives. It is intended as stand in for early adopters who work with rats
    and want to use the large shuttle drive
    - Update READMEs of other EIBs
2019-11-27 Add driver makefile and adapt main one
2019-12-07 headstage-neuropix rev 1.2
    - Dual neuropixels probe support
    - 2X HTC Vive receivers
    - Many changes made for reliability of manufacturing
2019-12-18 Updated C++ bindings to work with driver functionality
    - The context_t constructor now takes driver context option arguments
    that are needed before initialization using a variadic constructor.
    Option value pairs are provided using a driver_arg_t = std::pair<int, T>.
    - I also fixed some issues with the code when setting options that are
    pointer types to begin with, instead of non pointers. To do this, I made
    use of the C++17's if constexpr functionality
2020-01-07 Basic sizing for updated breakout board case
    - Needs fit check
    - Needs draft angles
    - Needs to be split in 2 parts
    - Add cutouts for laser cut top panels?
2020-02-06 headstage-64 rev. 1.4 along with all dependencies
    - This is headstage-64 revision 1.4. Because it involves a change in the
    bottom analog connector, a lot of other boards had to be changed to
    match the new pinout. That is why there are so many files in this
    commit. Changes in revision 1.4 and affects on other boards are as
    follows:
    1. The coaxial adapter board has been improved to allow a regulator to
2020-02-09 Remove erroneos LED values from silk layer of fmc-host
2020-03-09 Final headstage-neuropix rev. 1.2
    - BOM simplification while updating the google sheet
    - Small PCB changes
2020-04-15 Lock the handle when initializing riffa
2020-04-20 Add riffa lib VS project files
2020-05-07 Initial commit drive&headstage size & weight comparison
2020-06-02 More updates to headstage-neuropix after review from Speedy
    - Many bottom side pads moved apart to allow solder mask in between and
    to prevent shorts
2020-06-08 Added headstage-64/revisions/rev-1.3
    - Contains board designs, fab files, BOM, etc for headstage-64 rev 1.3,
    which is used in several labs and distributed with the beta-test kit
2020-06-08 Added frozen eib-64-large/revisions/rev-1.0
    - This is the beta-test version of eib-64-large
2020-06-09 Add SHA for test-board-64/revisions/rev-1.2
2020-07-02 clroni version 3.1.1
    - Replaced device map naming with device table
    - contex.DeviceTable is now a Dictionary rather than a List
    - Update nuget package
2020-07-13 Got rid of accidentally added temporary files
2020-08-03 Deprecate lighthouse-booster
    - We are moving the V2 of the lighthouse system which solves the range
    issue that the booster was meant to address
2020-08-10 Remove defunt .gitmodules
2020-09-01 Breakout case WIP
    non functional, needs to be updated to newer pcb
2020-09-04 Added waterejet DXF files for case to get quotes ready
2020-10-09 Increased space between IDC headers and wire terminals on breakout
    - Moved by 2mm so that an IDC connector can actually plug into the
    header.
2021-02-11 Added more room for caps in breakout case
    Changed circular cutouts on bottom side of the case facing the PCB to longer slots to make more room for components. Should fix issue that filipe just encountered on first test assembly for beta-test.
2021-03-16 Update breakout firmware README.md
    - Get rid of PLL info since its clearly visible in the code
2021-04-06 Fully functional breakout firmware
    - Integrated preprocessor switches into the code so that changes do not
    need to be made to run simulations
    - Digital input sampling now occurs on falling edge of LVDS_OUT[0] which
    put it 180 deg. out of phase with when its latched to prevent
    metastability
    - Other very small changes
2021-05-26 Add IRFML8244 N-MOSFET datasheet to breakout/datasheets
2021-05-30 Add archive notice to headstage-neuropix/README
    - Development has been moved to https://github.com/open-ephys/onix-headstage-neuropix1
